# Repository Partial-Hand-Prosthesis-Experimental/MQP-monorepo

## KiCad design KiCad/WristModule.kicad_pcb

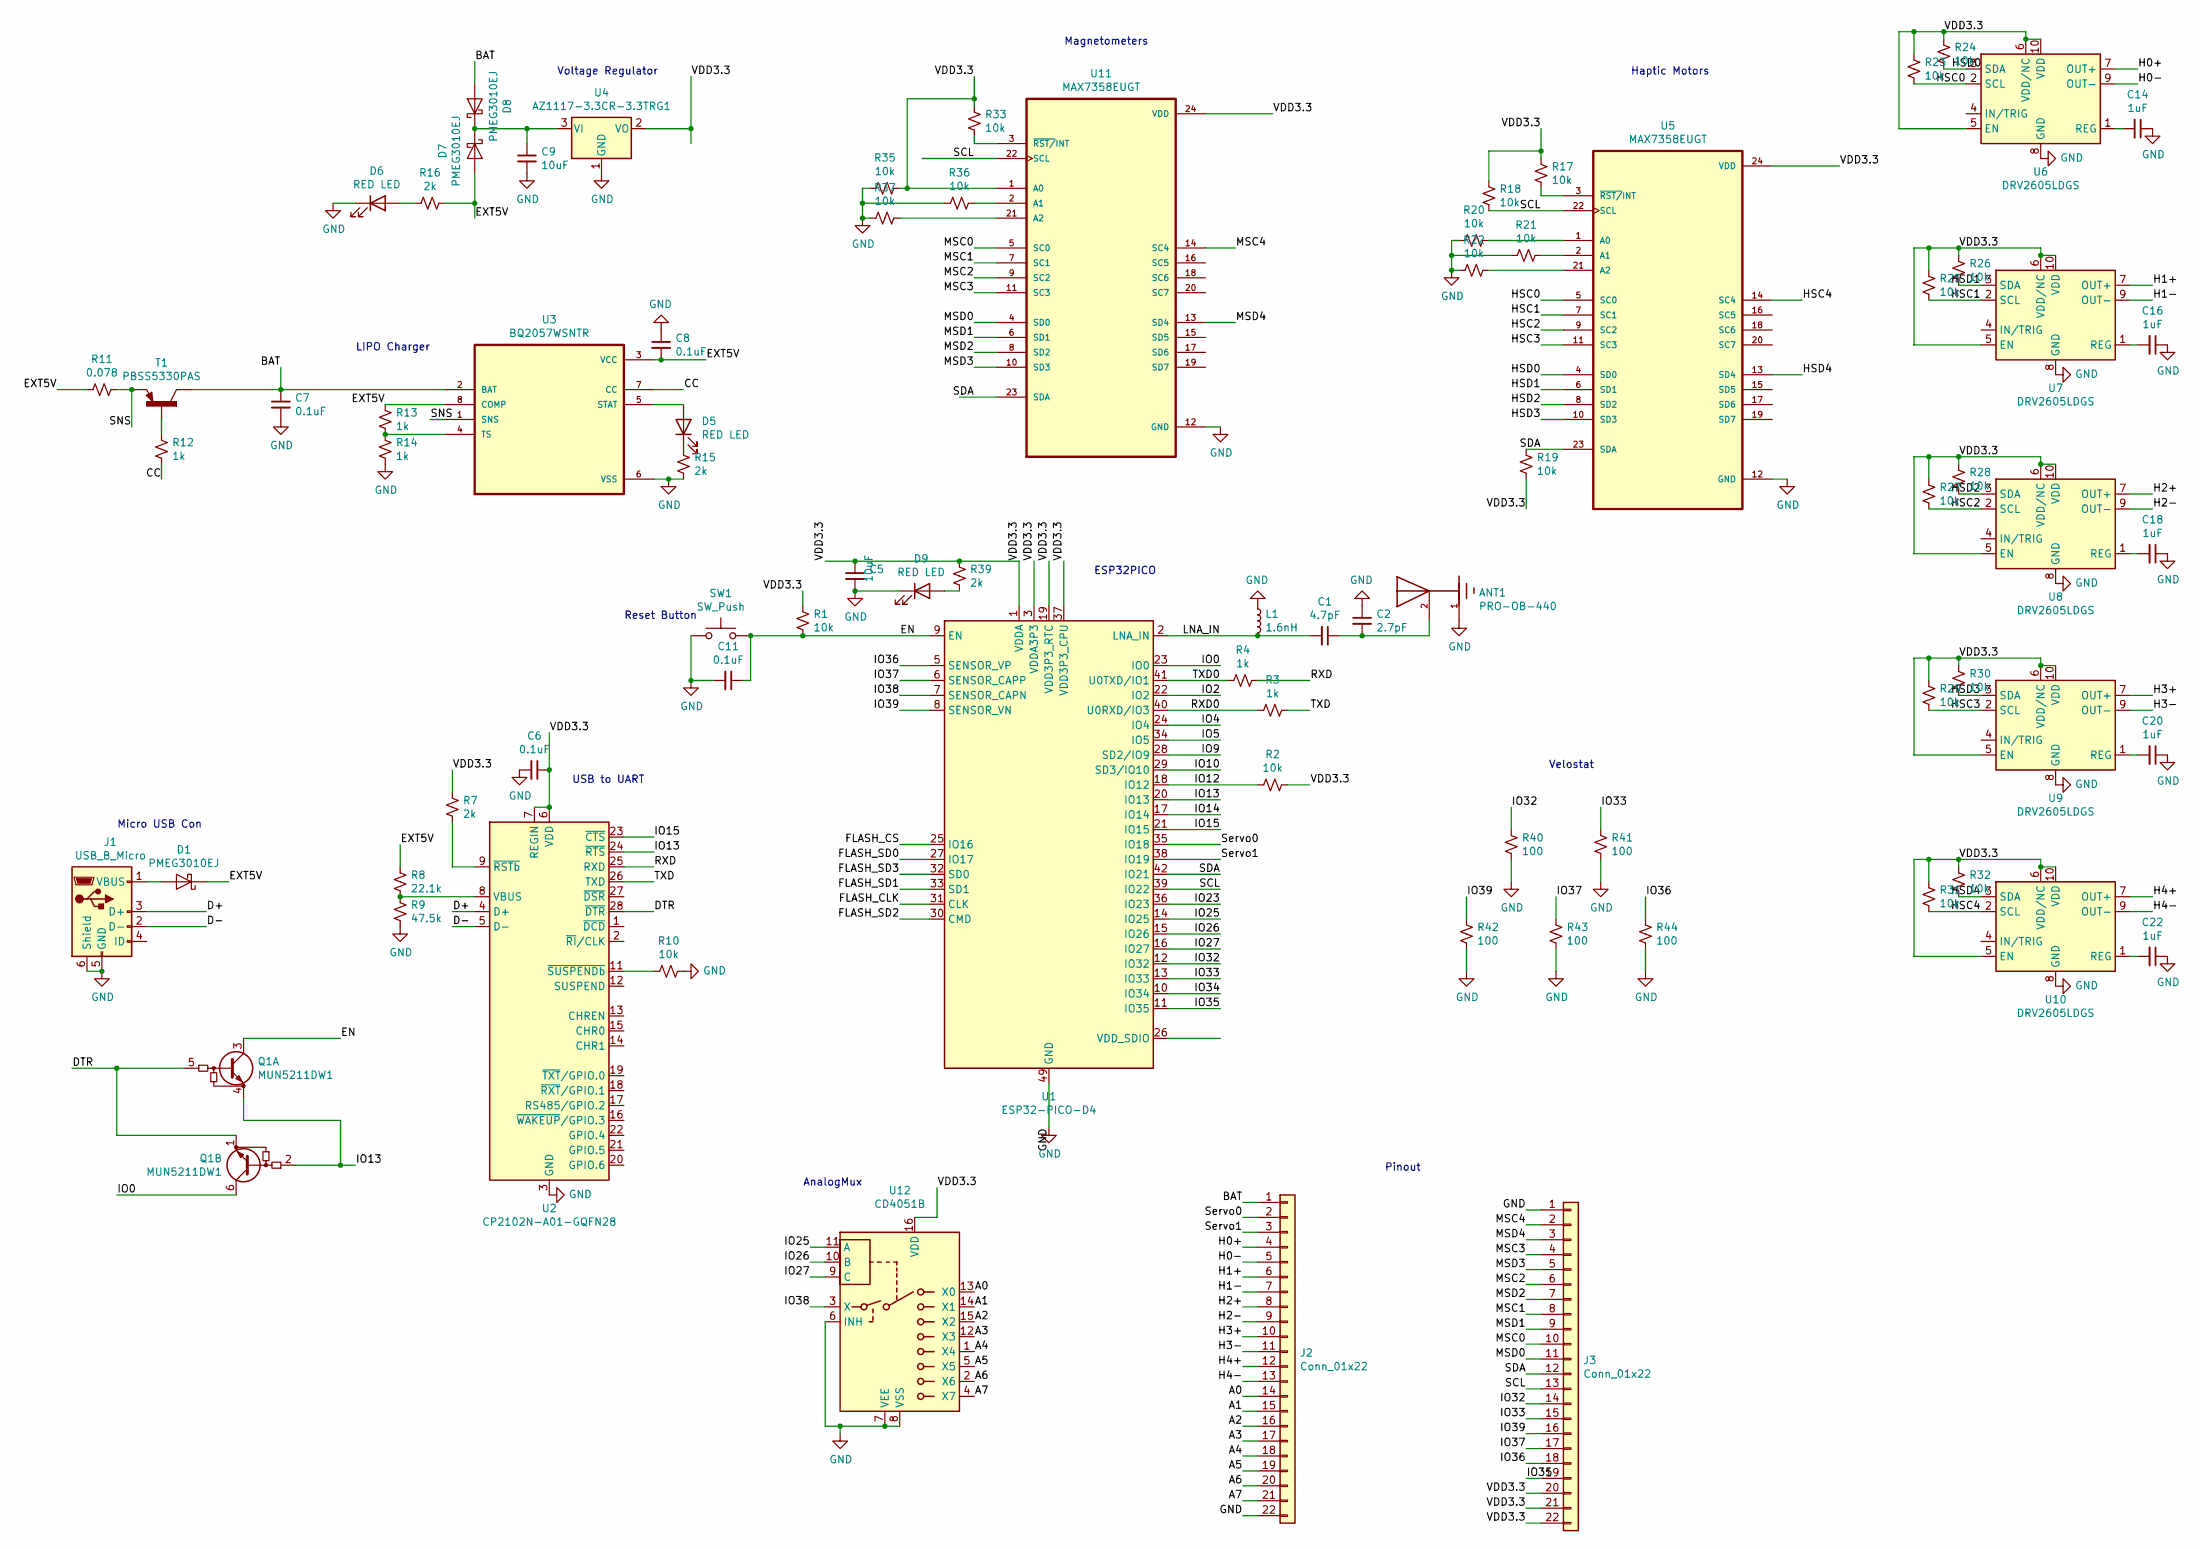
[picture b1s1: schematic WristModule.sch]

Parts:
ANT1: PRO-OB-440; ANT_PRO-OB-440; PARTREV 3.2
C1: 4.7pF; C_0201_0603Metric
C2: 2.7pF; C_0201_0603Metric
C5, C9: 10uF; C_0603_1608Metric
C6, C7, C8, C11: 0.1uF; C_0201_0603Metric
C14, C16, C18, C20, C22: 1uF; C_0201_0603Metric
D1, D7, D8: PMEG3010EJ; D_SOD-323F
D5, D6, D9: RED LED; D_0603_1608Metric
J1: USB_B_Micro; USB_Micro-B_Amphenol_10118194_Horizontal
J2, J3: Conn_01x22; PinHeader_1x22_P2.00mm_Vertical
L1: 1.6nH; L_0201_0603Metric
Q1: MUN5211DW1; SOT-363_SC-70-6
R1, R2, R10, R17, R18, R19, R20, R21, R22, R23, R24, R25, R26, R27, R28, R29, R30, R31, R32, R33, R35, R36, R37: 10k; R_0201_0603Metric
R3, R4, R12, R13, R14: 1k; R_0201_0603Metric
R7, R15, R16, R39: 2k; R_0201_0603Metric
R8: 22.1k; R_0201_0603Metric
R9: 47.5k; R_0201_0603Metric
R11: 0.078; R_0402_1005Metric
R40, R41, R42, R43, R44: 100; R_0201_0603Metric
SW1: SW_Push; SW_Push_1P1T_NO_Vertical_Wuerth_434133025816
T1: PBSS5330PAS; SOT1061D
U1: ESP32-PICO-D4; QFN-48-1EP_7x7mm_P0.5mm_EP5.3x5.3mm
U2: CP2102N-A01-GQFN28; QFN-28-1EP_5x5mm_P0.5mm_EP3.35x3.35mm
U3: BQ2057WSNTR; SOIC127P599X175-8N
U4: AZ1117-3.3CR-3.3TRG1; SOT150P410X160-3N
U5, U11: MAX7358EUGT; SOP65P640X110-24N
U6, U7, U8, U9, U10: DRV2605LDGS; VSSOP-10_3x3mm_P0.5mm
U12: CD4051B; TSSOP-16_4.4x5mm_P0.65mm

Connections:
/A0: J2.14, U12.13 (X0)
/A1: J2.15, U12.14 (X1)
/A2: J2.16, U12.15 (X2)
/A3: J2.17, U12.12 (X3)
/A4: J2.18, U12.1 (X4)
/A5: J2.19, U12.5 (X5)
/A6: J2.20, U12.2 (X6)
/A7: J2.21, U12.4 (X7)
/BAT: C7.1, D8.2 (A), J2.1, T1.3, U3.2 (BAT)
/CC: R12.2, U3.7 (CC)
/D+: J1.3 (D+), U2.4 (D+)
/D-: J1.2 (D-), U2.5 (D-)
/DTR: Q1.1 (E2), Q1.5 (B1), U2.28 (~DTR)
/EN: C11.1, Q1.3 (C1), R1.2, SW1.2, U1.9 (EN)
/EXT5V: C8.2, D1.1 (K), D7.2 (A), R8.1, R11.2, R13.1, R16.1, U3.3 (VCC), U3.8 (COMP)
/FLASH_CLK: U1.31 (CLK)
/FLASH_CS: U1.25 (IO16)
/FLASH_SD0: U1.27 (IO17)
/FLASH_SD1: U1.33 (SD1)
/FLASH_SD2: U1.30 (CMD)
/FLASH_SD3: U1.32 (SD0)
/H0+: J2.4, U6.7 (OUT+)
/H0-: J2.5, U6.9 (OUT-)
/H1+: J2.6, U7.7 (OUT+)
/H1-: J2.7, U7.9 (OUT-)
/H2+: J2.8, U8.7 (OUT+)
/H2-: J2.9, U8.9 (OUT-)
/H3+: J2.10, U9.7 (OUT+)
/H3-: J2.11, U9.9 (OUT-)
/H4+: J2.12, U10.7 (OUT+)
/H4-: J2.13, U10.9 (OUT-)
/HSC0: R23.2, U5.5 (SC0), U6.2 (SCL)
/HSC1: R25.2, U5.7 (SC1), U7.2 (SCL)
/HSC2: R27.2, U5.9 (SC2), U8.2 (SCL)
/HSC3: R29.2, U5.11 (SC3), U9.2 (SCL)
/HSC4: R31.2, U5.14 (SC4), U10.2 (SCL)
/HSD0: R24.2, U5.4 (SD0), U6.3 (SDA)
/HSD1: R26.2, U5.6 (SD1), U7.3 (SDA)
/HSD2: R28.2, U5.8 (SD2), U8.3 (SDA)
/HSD3: R30.2, U5.10 (SD3), U9.3 (SDA)
/HSD4: R32.2, U5.13 (SD4), U10.3 (SDA)
/IO0: Q1.6 (C2), U1.23 (IO0)
/IO2: U1.22 (IO2)
/IO4: U1.24 (IO4)
/IO5: U1.34 (IO5)
/IO9: U1.28 (SD2/IO9)
/IO10: U1.29 (SD3/IO10)
/IO12: R2.2, U1.18 (IO12)
/IO13: Q1.2 (B2), Q1.4 (E1), U1.20 (IO13), U2.24 (~RTS)
/IO14: U1.17 (IO14)
/IO15: U1.21 (IO15), U2.23 (~CTS)
/IO23: U1.36 (IO23)
/IO25: U1.14 (IO25), U12.11 (A)
/IO26: U1.15 (IO26), U12.10 (B)
/IO27: U1.16 (IO27), U12.9 (C)
/IO32: J3.14, R40.1, U1.12 (IO32)
/IO33: J3.15, R41.1, U1.13 (IO33)
/IO34: U1.10 (IO34)
/IO35: J3.19, U1.11 (IO35)
/IO36: J3.18, R44.1, U1.5 (SENSOR_VP)
/IO37: J3.17, R43.1, U1.6 (SENSOR_CAPP)
/IO38: U1.7 (SENSOR_CAPN), U12.3 (X)
/IO39: J3.16, R42.1, U1.8 (SENSOR_VN)
/LNA_IN: C1.2, L1.2, U1.2 (LNA_IN)
/MSC0: J3.10, U11.5 (SC0)
/MSC1: J3.8, U11.7 (SC1)
/MSC2: J3.6, U11.9 (SC2)
/MSC3: J3.4, U11.11 (SC3)
/MSC4: J3.2, U11.14 (SC4)
/MSD0: J3.11, U11.4 (SD0)
/MSD1: J3.9, U11.6 (SD1)
/MSD2: J3.7, U11.8 (SD2)
/MSD3: J3.5, U11.10 (SD3)
/MSD4: J3.3, U11.13 (SD4)
/RXD: R4.1, U2.25 (RXD)
/RXD0: R3.2, U1.40 (U0RXD/IO3)
/SCL: J3.13, R18.2, U1.39 (IO22), U5.22 (SCL), U11.22 (SCL)
/SDA: J3.12, R19.1, U1.42 (IO21), U5.23 (SDA), U11.23 (SDA)
/SNS: R11.1, T1.2, U3.1 (SNS)
/Servo0: J2.2, U1.35 (IO18)
/Servo1: J2.3, U1.38 (IO19)
/TXD: R3.1, U2.26 (TXD)
/TXD0: R4.2, U1.41 (U0TXD/IO1)
/VDD3.3: C5.1, C6.1, J3.20, J3.21, J3.22, R1.1, R2.1, R7.1, R17.1, R18.1, R19.2, R23.1, R24.1, R25.1, R26.1, R27.1, R28.1, R29.1, R30.1, R31.1, R32.1, R33.1, R35.1, R39.1, U1.1 (VDDA), U1.3 (VDDA3P3), U1.4 (VDDA3P3), U1.19 (VDD3P3_RTC), U1.37 (VDD3P3_CPU), U1.43 (VDDA), U1.46 (VDDA), U2.6 (VDD), U2.7 (REGIN), U4.2 (VO), U5.24 (VDD), U6.5 (EN), U6.6 (VDD/NC), U6.10 (VDD), U7.5 (EN), U7.6 (VDD/NC), U7.10 (VDD), U8.5 (EN), U8.6 (VDD/NC), U8.10 (VDD), U9.5 (EN), U9.6 (VDD/NC), U9.10 (VDD), U10.5 (EN), U10.6 (VDD/NC), U10.10 (VDD), U11.1 (A0), U11.24 (VDD), U12.16 (VDD)
GND: ANT1.1, C2.1, C5.2, C6.2, C7.2, C8.1, C9.2, C11.2, C14.1, C16.1, C18.1, C20.1, C22.1, D6.1 (K), D9.1 (K), J1.5 (GND), J1.6 (Shield), J2.22, J3.1, L1.1, R9.2, R10.1, R14.2, R15.2, R20.2, R21.2, R22.2, R35.2, R36.2, R37.2, R40.2, R41.2, R42.2, R43.2, R44.2, SW1.1, U1.49 (GND), U2.3 (GND), U2.29 (GND), U3.6 (VSS), U4.1 (GND), U5.12 (GND), U6.8 (GND), U7.8 (GND), U8.8 (GND), U9.8 (GND), U10.8 (GND), U11.12 (GND), U12.6 (INH), U12.7 (VEE), U12.8 (VSS)
unnamed: ANT1.2, C1.1, C2.2
unnamed: C9.1, D7.1 (K), D8.1 (K), U4.3 (VI)
unnamed: C14.2, U6.1 (REG)
unnamed: C16.2, U7.1 (REG)
unnamed: C18.2, U8.1 (REG)
unnamed: C20.2, U9.1 (REG)
unnamed: C22.2, U10.1 (REG)
unnamed: D1.2 (A), J1.1 (VBUS)
unnamed: D5.1 (K), R15.1
unnamed: D5.2 (A), U3.5 (STAT)
unnamed: D6.2 (A), R16.2
unnamed: D9.2 (A), R39.2
unnamed: R7.2, U2.9 (~RSTb)
unnamed: R8.2, R9.1, U2.8 (VBUS)
unnamed: R10.2, U2.11 (~SUSPENDb)
unnamed: R12.1, T1.1
unnamed: R13.2, R14.1, U3.4 (TS)
unnamed: R17.2, U5.3 (~RST/~INT)
unnamed: R20.1, U5.1 (A0)
unnamed: R21.1, U5.2 (A1)
unnamed: R22.1, U5.21 (A2)
unnamed: R33.2, U11.3 (~RST/~INT)
unnamed: R36.1, U11.2 (A1)
unnamed: R37.1, U11.21 (A2)

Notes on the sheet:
LIPO Charger
Voltage Regulator
Micro USB Con
USB to UART
Reset Button
AnalogMux
Pinout
Magnetometers
Haptic Motors
Velostat
ESP32PICO

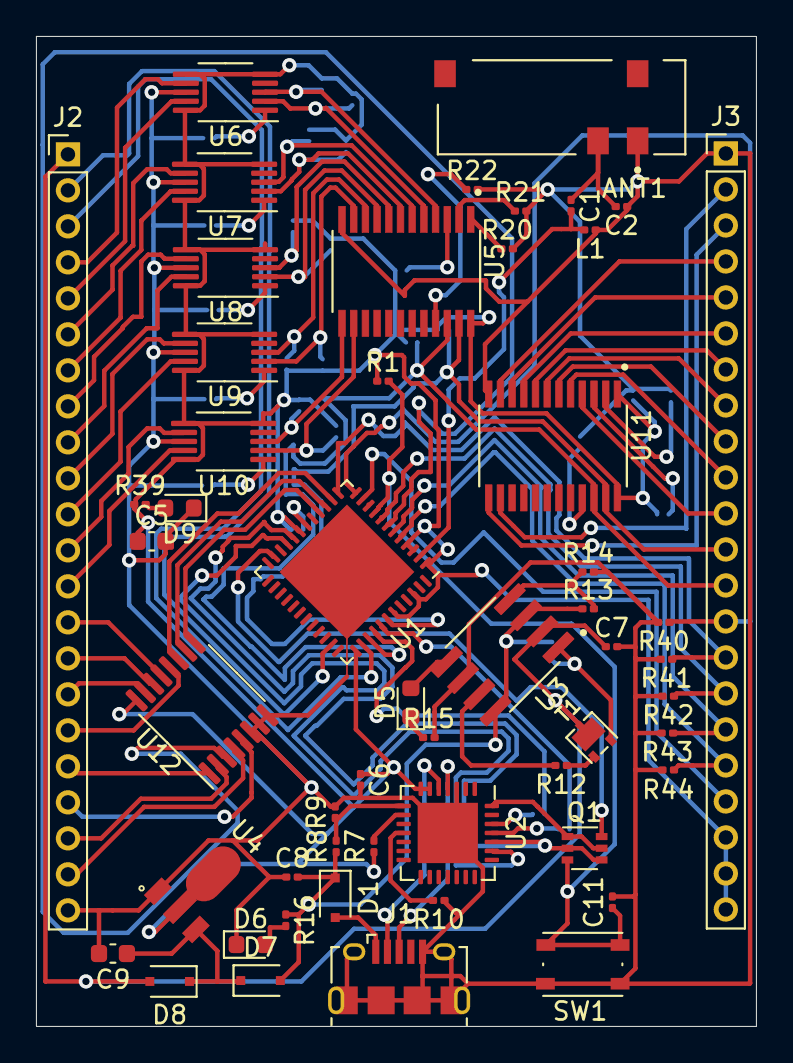
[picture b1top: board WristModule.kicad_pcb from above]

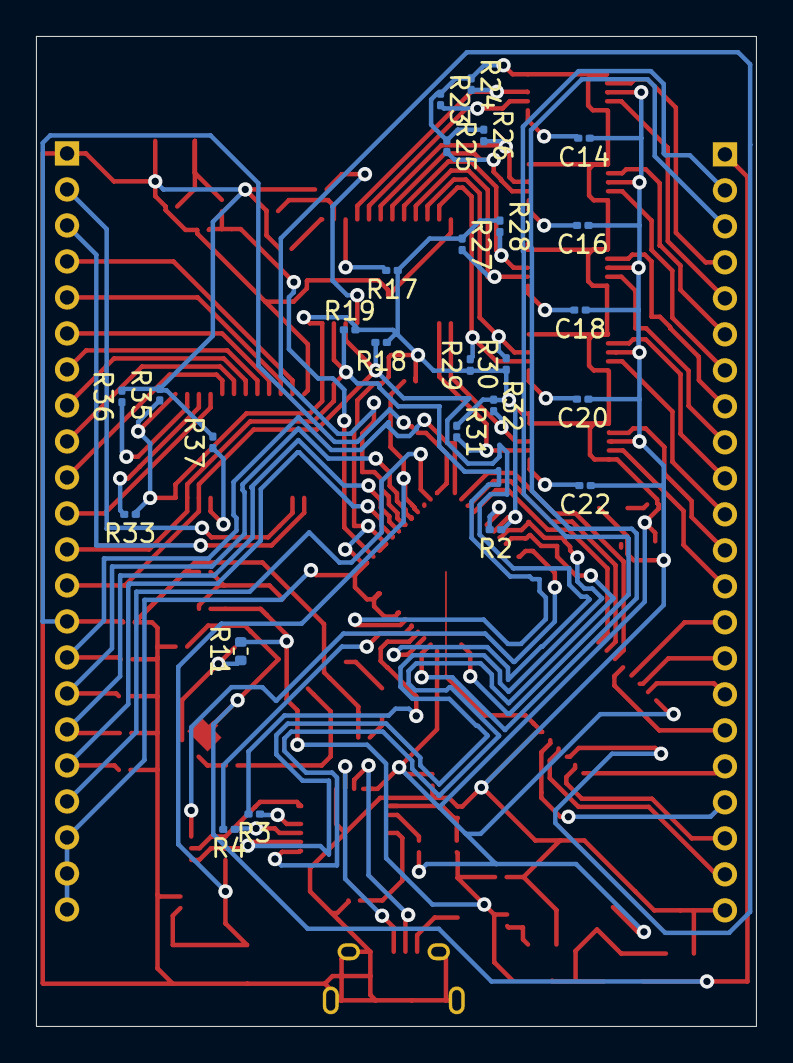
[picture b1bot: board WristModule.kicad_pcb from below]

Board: 2 copper layers, 40.0 x 55.0 mm, 79 parts (26 on the bottom side), 95 nets.

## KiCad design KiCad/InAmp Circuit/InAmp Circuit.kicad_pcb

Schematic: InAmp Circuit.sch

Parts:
C1, C2, C3, C4, C5: 4.7uF; C_0805_2012Metric_Pad1.18x1.45mm_HandSolder
INA1, INA2, INA3, INA4, INA5: INA122U; SOIC127P599X175-8N
J1: Conn_01x12; PinHeader_1x12_P2.54mm_Vertical
J2: Conn_01x05; PinHeader_1x05_P2.54mm_Vertical
R1, R2, R3, R4, R5: 1k Ohm; R_0805_2012Metric_Pad1.20x1.40mm_HandSolder
Ref1, Ref2, Ref3, Ref4, Ref5: 200 Ohm; R_0805_2012Metric_Pad1.20x1.40mm_HandSolder

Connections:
1: C1.1, C2.1, C3.1, C4.1, C5.1, INA1.3, INA1.7, INA2.3, INA2.7, INA3.3, INA3.7, INA4.3, INA4.7, INA5.3, INA5.7, J1.3, J1.5, J1.7, J1.9, J1.11, J1.12
2: C1.2, INA1.2, J1.2, R1.1
4: C2.2, INA2.2, J1.4, R2.1
6: C3.2, INA3.2, J1.6, R3.1
8: C4.2, INA4.2, J1.8, R4.1
10: C5.2, INA5.2, J1.10, R5.1
GND: INA1.4, INA1.5, INA2.4, INA2.5, INA3.4, INA3.5, INA4.4, INA4.5, INA5.4, INA5.5, J1.1, R1.2, R2.2, R3.2, R4.2, R5.2
unnamed: INA1.1, INA1.8, Ref1.1, Ref1.2
unnamed: INA2.1, INA2.8, Ref2.1, Ref2.2
unnamed: INA3.1, INA3.8, Ref3.1, Ref3.2
unnamed: INA4.1, INA4.8, Ref4.1, Ref4.2
unnamed: INA5.1, INA5.8, Ref5.1, Ref5.2
O1: INA1.6, J2.1
O2: INA2.6, J2.2
O3: INA3.6, J2.3
O4: INA4.6, J2.4
O5: INA5.6, J2.5

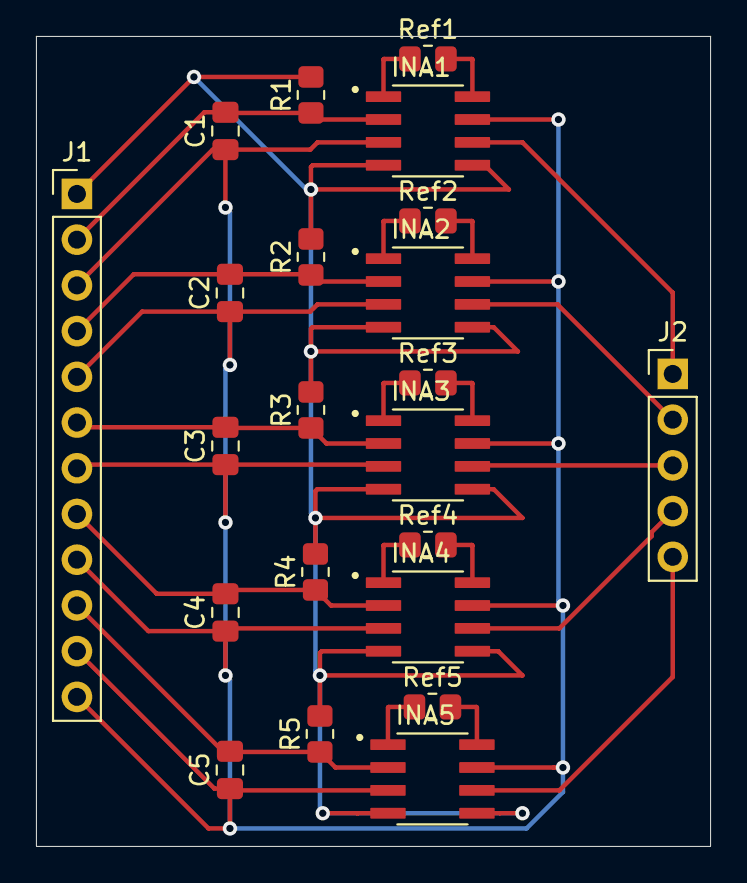
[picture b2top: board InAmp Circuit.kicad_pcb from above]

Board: 2 copper layers, 37.4 x 45.0 mm, 22 parts (0 on the bottom side), 17 nets.

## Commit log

2022-01-03 BLE multifloat notify
2022-01-10 add 2way comms
2022-01-10 Working 3d plot
2022-02-08 update hand vis
2022-02-08 track reskin
2022-02-16 Add uint8 passing between uC and web
2022-02-20 Added velostat to haptic code
2022-02-23 Added InAmp KiCAD board and schematic
    Also added folder for downloaded footprints and symbols
2022-02-23 Added InAmp KiCad files and supporting symbols and footprints
2022-02-23 Add vibrohaptics with mux
2022-04-10 Added other Third Party KiCAD parts
2022-04-10 Migrate Haptics
2022-04-10 Wrist Mod PCB files
2022-04-13 Add ISR
2022-04-13 Track old datagrabs
2022-04-13 clean workspace
2022-04-13 Set MTU back to 20 for windows
2022-04-13 FF hand-toy
2022-04-14 added KNN and Kalman Filters, still WIP
2022-04-14 compiles. fully integratese knn and kalman filters
2022-04-15 tested knn
2022-04-15 about to try making knn out of all smaples
2022-04-15 working position estimate
2022-04-15 working and ajsusting pos kalman filter based on knn confdence
2022-04-16 Add PI and PID controllers
2022-04-16 bump hand-toy
2022-04-16 sycnch
2022-04-16 Add GMM library
2022-04-16 Globals
2022-04-16 Library added, builds
2022-04-16 housekeeping
2022-04-16 Vibe Conf better persist
2022-04-16 Fix crash from bad ISR
2022-04-16 velosat state machine
2022-04-16 fixed compile issues
2022-04-16 im the map
2022-04-16 mapp merge
2022-04-16 PID with some filtering
2022-04-16 synch
2022-04-16 this is fine
2022-04-16 abandoning, trying km
2022-04-16 working gmm clasifier though pointers
2022-04-16 working hall and vs clasifiers
2022-04-16 vs kalman
2022-04-16 investigating vs reading error
2022-04-16 moving to LED
2022-04-16 LED failed
2022-04-19 Half-finished haptic, log hallPos
2022-04-20 Remap for pico32 setup
2022-04-22 Add modes
2022-04-22 Always persist vib state
2022-04-22 Retune PID for 8.4v
2022-04-22 Make vel+torque not identical
2022-04-22 added tactile print statements
2022-04-22 Current print
